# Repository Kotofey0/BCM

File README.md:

# BCM
DIY Body Control Module software for BMW E87 with 1JZ.
Main function - connect Kombi to EMS and powertrain sensors.
Additional - controlling lights, windows, SZL etc.
## C project
Root folder is a STM32Cube project
## EAGLE project
Schematic and PCB files are in **.eagle** folder. Used libraries are in **lbr** folder. 
## References
- [E90 Dashboard ETS2](https://github.com/Marcin648/e90-dashboard-ets2)
- [BMW Can-bus Codes](http://www.loopybunny.co.uk/CarPC/k_can.html)

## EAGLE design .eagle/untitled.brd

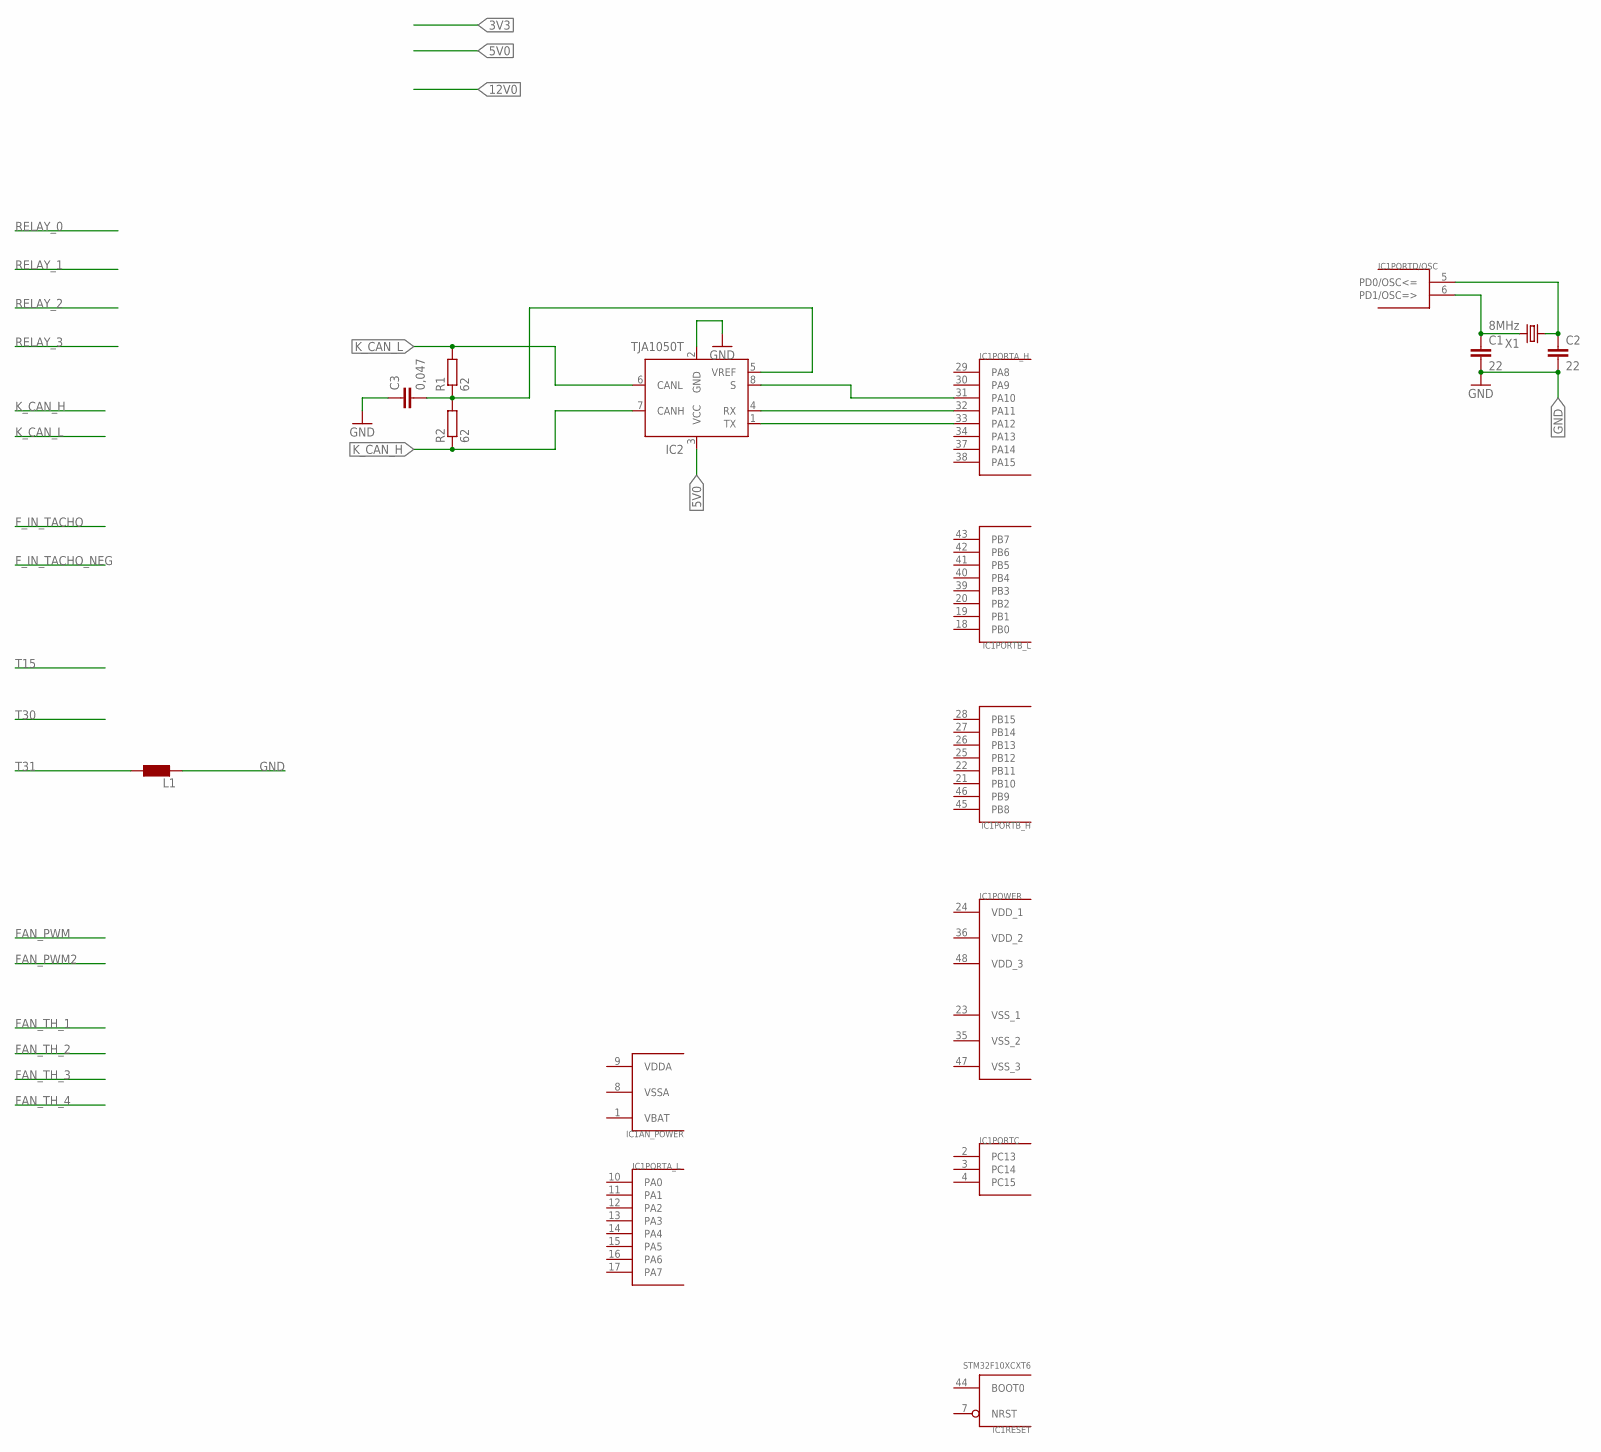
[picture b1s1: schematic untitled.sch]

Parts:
C1, C2: 22; C0805
C3: 0,047; C0805
IC1: STM32F10XCXT6; TQFP48
IC2: TJA1050T; SOIC8
L1: L0204/7; 0204/7
R1, R2: 62; M0805
X1: 8MHz; HC49

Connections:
5V0: IC2.3 (VCC)
GND: C1.2, C2.2, C3.1, IC2.2 (GND), L1.2
K_CAN_H: IC2.7 (CANH), R2.1
K_CAN_L: IC2.6 (CANL), R1.2
unnamed: C1.1, IC1.6 (PD1/OSC=>), X1.2
unnamed: C2.1, IC1.5 (PD0/OSC<=), X1.1
unnamed: IC1.32 (PA11), IC2.4 (RX)
unnamed: IC1.33 (PA12), IC2.1 (TX)
unnamed: IC1.31 (PA10), IC2.8 (S)
unnamed: C3.2, IC2.5 (VREF), R1.1, R2.2
T31: L1.1
VBAT: IC1.1 (VBAT)
VDDA: IC1.9 (VDDA)
VDD_1: IC1.24 (VDD_1)
VDD_2: IC1.36 (VDD_2)
VDD_3: IC1.48 (VDD_3)
VSSA: IC1.8 (VSSA)
VSS_1: IC1.23 (VSS_1)
VSS_2: IC1.35 (VSS_2)
VSS_3: IC1.47 (VSS_3)

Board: 2 copper layers, 9 parts (0 on the bottom side), 9 nets, no tracks yet.

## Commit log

2023-06-28 initial
2023-06-28 test
2023-06-28 github sync attempt 2
2023-06-28 Kombi CAN added
2023-06-28 Kombi works
2023-07-11 Меняю камень
2023-07-11 Switch MCU
2023-07-11 last fix tonight
2023-07-11 last fix tonight 2
